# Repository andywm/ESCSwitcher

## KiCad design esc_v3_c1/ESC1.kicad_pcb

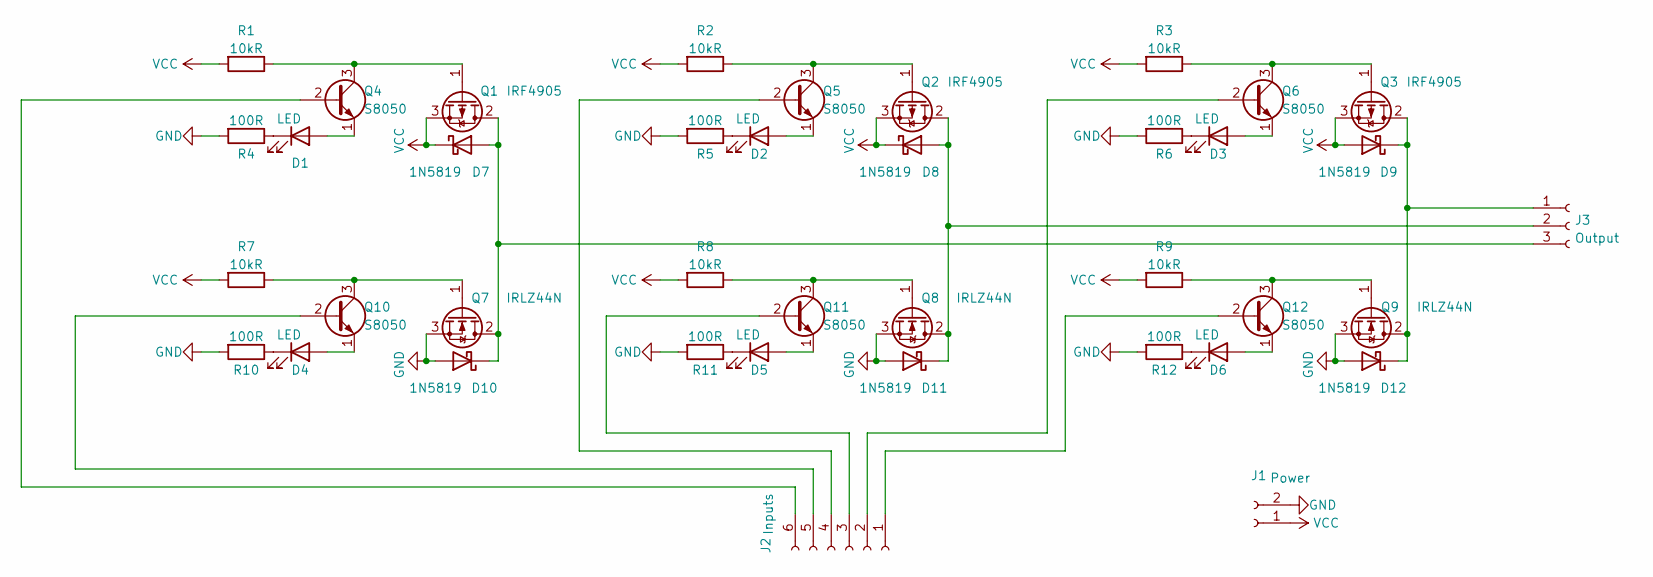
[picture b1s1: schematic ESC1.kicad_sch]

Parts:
D1, D2, D3, D4, D5, D6: LED; LED_D3.0mm_Clear
D7, D8, D9: 1N5819; D_DO-41_SOD81_P3.81mm_Vertical_AnodeUp
D10, D11, D12: 1N5819; D_DO-41_SOD81_P3.81mm_Vertical_KathodeUp
J1: Power; JST_XH_B2B-XH-A_1x02_P2.50mm_Vertical
J2: Inputs; JST_XH_B6B-XH-A_1x06_P2.50mm_Vertical
J3: Output; JST_XH_B3B-XH-A_1x03_P2.50mm_Vertical
Q1, Q2, Q3: IRF4905; TO-220-3_Vertical
Q4, Q5, Q6, Q10, Q11, Q12: S8050; TO-92_Inline
Q7, Q8, Q9: IRLZ44N; TO-220-3_Vertical
R1, R2, R3, R7, R8, R9: 10kR; R_Axial_DIN0309_L9.0mm_D3.2mm_P15.24mm_Horizontal
R4, R5, R6, R10, R11, R12: 100R; R_Axial_DIN0309_L9.0mm_D3.2mm_P15.24mm_Horizontal

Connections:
GND: D10.2 (A), D11.2 (A), D12.2 (A), J1.2, Q7.3 (S), Q8.3 (S), Q9.3 (S), R4.2, R5.2, R6.2, R10.2, R11.2, R12.2
unnamed: D1.1 (K), R4.1
unnamed: D1.2 (A), Q4.1 (E)
unnamed: D2.1 (K), R5.1
unnamed: D2.2 (A), Q5.1 (E)
unnamed: D3.1 (K), R6.1
unnamed: D3.2 (A), Q6.1 (E)
unnamed: D4.1 (K), R10.1
unnamed: D4.2 (A), Q10.1 (E)
unnamed: D5.1 (K), R11.1
unnamed: D5.2 (A), Q11.1 (E)
unnamed: D6.1 (K), R12.1
unnamed: D6.2 (A), Q12.1 (E)
unnamed: D7.2 (A), D10.1 (K), J3.3, Q1.2 (D), Q7.2 (D)
unnamed: D8.2 (A), D11.1 (K), J3.2, Q2.2 (D), Q8.2 (D)
unnamed: D9.1 (K), D12.1 (K), J3.1, Q3.2 (D), Q9.2 (D)
unnamed: J2.1, Q12.2 (B)
unnamed: J2.2, Q6.2 (B)
unnamed: J2.3, Q11.2 (B)
unnamed: J2.4, Q5.2 (B)
unnamed: J2.5, Q10.2 (B)
unnamed: J2.6, Q4.2 (B)
unnamed: Q1.1 (G), Q4.3 (C), R1.1
unnamed: Q2.1 (G), Q5.3 (C), R2.1
unnamed: Q3.1 (G), Q6.3 (C), R3.1
unnamed: Q7.1 (G), Q10.3 (C), R7.1
unnamed: Q8.1 (G), Q11.3 (C), R8.1
unnamed: Q9.1 (G), Q12.3 (C), R9.1
VCC: D7.1 (K), D8.1 (K), D9.2 (A), J1.1, Q1.3 (S), Q2.3 (S), Q3.3 (S), R1.2, R2.2, R3.2, R7.2, R8.2, R9.2

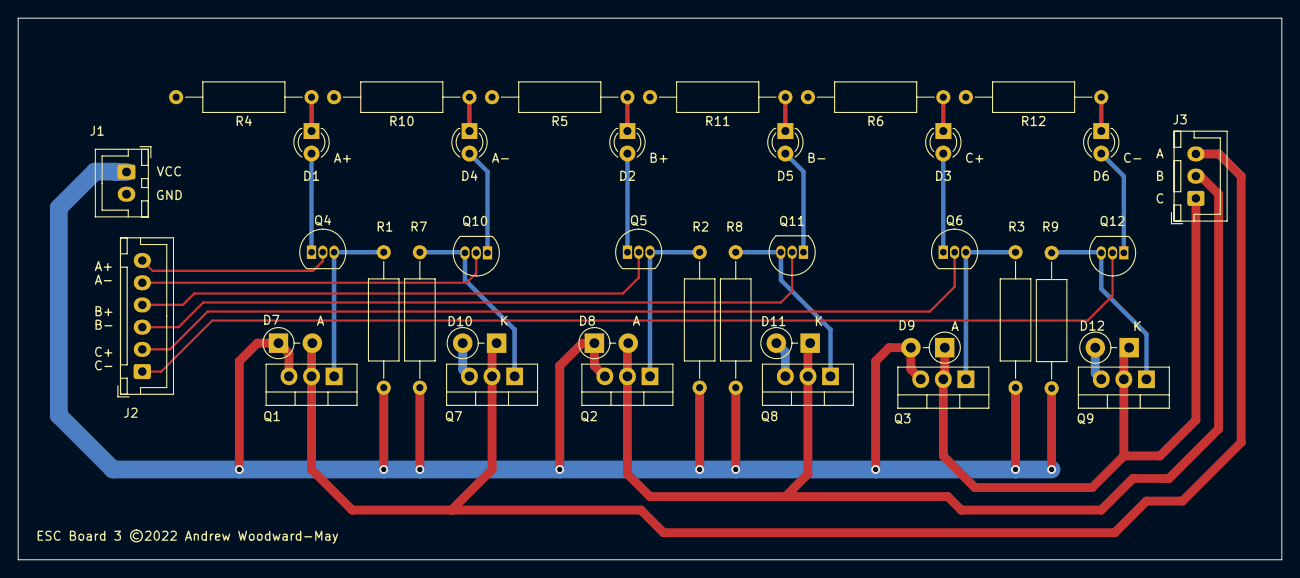
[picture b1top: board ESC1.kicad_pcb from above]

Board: 2 copper layers, 142.2 x 61.0 mm, 39 parts (0 on the bottom side), 29 nets.

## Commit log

2022-02-26 add circuit design for switcher circuit
2022-03-05 populate initial board layout
2022-03-05 remove corrupted version
2022-03-05 fix n channel driver
2022-03-12 add plot files
2022-03-12 merge.. but the right thing

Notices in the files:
esc_v3_c1/ESC1.kicad_pcb:
ESC Board 3 ©2022 Andrew Woodward-May
